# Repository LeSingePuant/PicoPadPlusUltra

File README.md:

# PicoPadPlusUltra
For convenience, these individual Gerbers are ready for upload to a PCB manufactoring website.

Feel free to clone, fork, or help me polish my keyboard/macropad design.
If you do clone, fork, or order the PicoPadPlusUltra, please let me know via Twitter or Reddit via DM or a mention. 

Cheers!

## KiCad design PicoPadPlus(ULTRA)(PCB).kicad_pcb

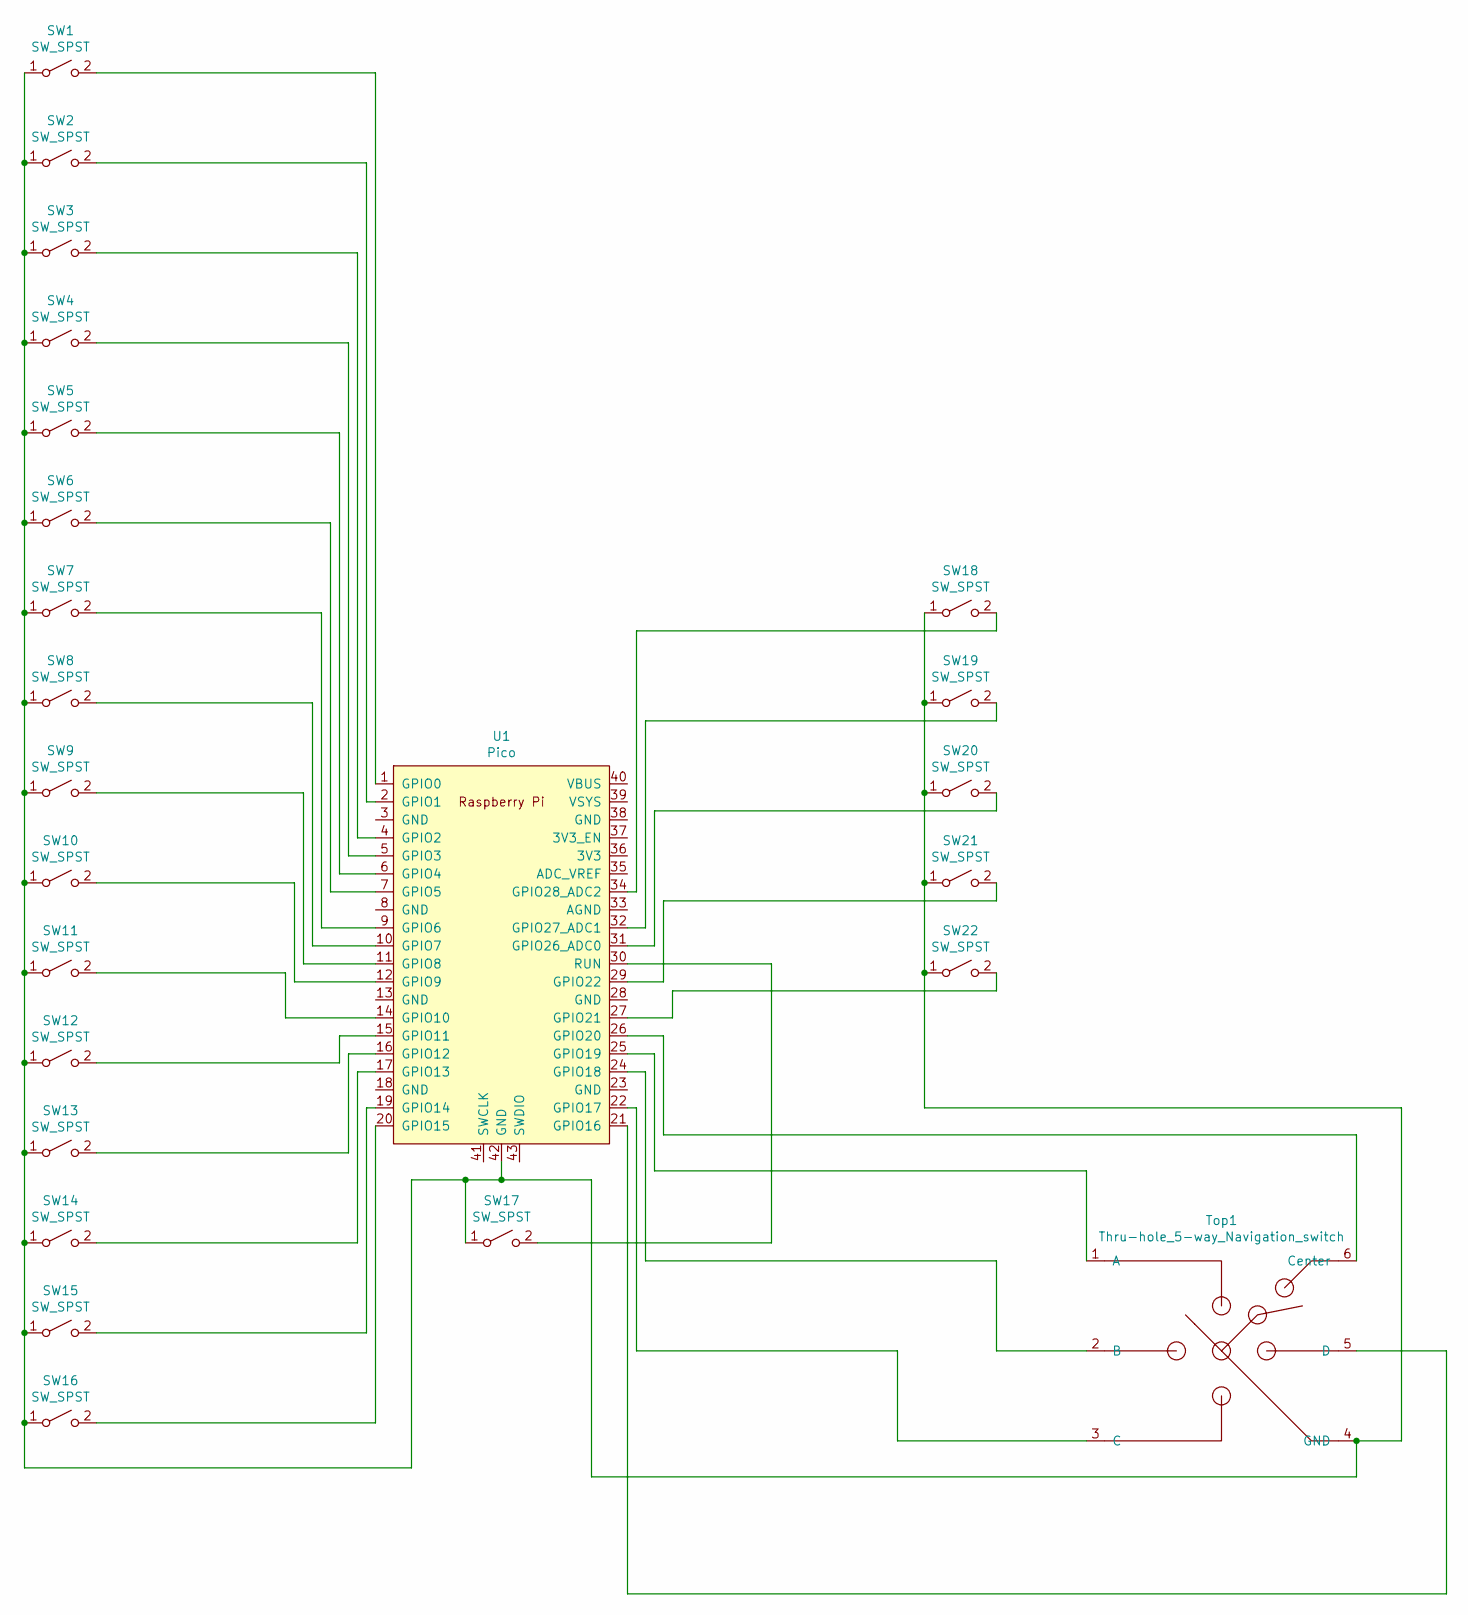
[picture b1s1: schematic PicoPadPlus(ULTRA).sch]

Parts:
SW1, SW2, SW3, SW4, SW5, SW6, SW7, SW8, SW9, SW10, SW11, SW12, SW13, SW14, SW15, SW16, SW18, SW19, SW20, SW21, SW22: SW_SPST; Kailh_socket_MX
SW17: SW_SPST; SW_PUSH_6mm
Top1: Thru-hole_5-way_Navigation_switch; SKQUCAA010_4-directional_with_Center_Push
U1: Pico; RPi_Pico_SMD_TH

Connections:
unnamed 0: SW1.1 (A), SW2.1 (A), SW3.1 (A), SW4.1 (A), SW5.1 (A), SW6.1 (A), SW7.1 (A), SW8.1 (A), SW9.1 (A), SW10.1 (A), SW11.1 (A), SW12.1 (A), SW13.1 (A), SW14.1 (A), SW15.1 (A), SW16.1 (A), SW17.1 (A), SW18.1 (A), SW19.1 (A), SW20.1 (A), SW21.1 (A), SW22.1 (A), Top1.4 (GND), U1.42 (GND); also elsewhere on the board
unnamed: SW1.2 (B), U1.1 (GPIO0)
unnamed: SW2.2 (B), U1.2 (GPIO1)
unnamed: SW3.2 (B), U1.4 (GPIO2)
unnamed: SW4.2 (B), U1.5 (GPIO3)
unnamed: SW5.2 (B), U1.6 (GPIO4)
unnamed: SW6.2 (B), U1.7 (GPIO5)
unnamed: SW7.2 (B), U1.9 (GPIO6)
unnamed: SW8.2 (B), U1.10 (GPIO7)
unnamed: SW9.2 (B), U1.11 (GPIO8)
unnamed: SW10.2 (B), U1.12 (GPIO9)
unnamed: SW11.2 (B), U1.14 (GPIO10)
unnamed: SW12.2 (B), U1.15 (GPIO11)
unnamed: SW13.2 (B), U1.16 (GPIO12)
unnamed: SW14.2 (B), U1.17 (GPIO13)
unnamed: SW15.2 (B), U1.19 (GPIO14)
unnamed: SW16.2 (B), U1.20 (GPIO15)
unnamed 17: SW17.2 (B), U1.30 (RUN); also elsewhere on the board
unnamed: SW18.2 (B), U1.34 (GPIO28_ADC2)
unnamed: SW19.2 (B), U1.32 (GPIO27_ADC1)
unnamed: SW20.2 (B), U1.31 (GPIO26_ADC0)
unnamed: SW21.2 (B), U1.29 (GPIO22)
unnamed: SW22.2 (B), U1.27 (GPIO21)
unnamed: Top1.1 (A), U1.25 (GPIO19)
unnamed: Top1.2 (B), U1.24 (GPIO18)
unnamed: Top1.3 (C), U1.22 (GPIO17)
unnamed: Top1.5 (D), U1.21 (GPIO16)
unnamed: Top1.6 (Center), U1.26 (GPIO20)

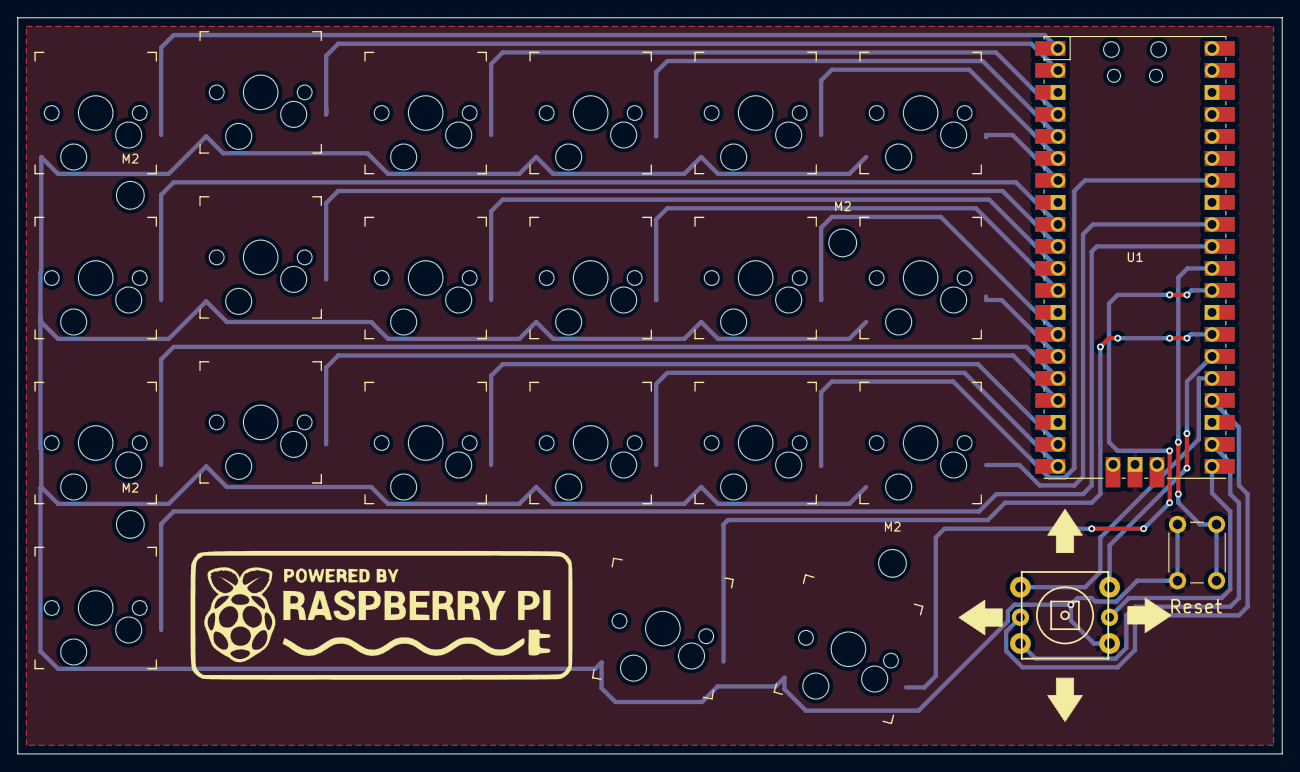
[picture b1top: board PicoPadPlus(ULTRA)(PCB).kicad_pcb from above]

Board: 2 copper layers, 146.0 x 85.0 mm, 28 parts (0 on the bottom side), 28 nets.

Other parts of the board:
M2, M2#2, M2#3, M2#4: MountingHole_3.2mm_M3
Reset: SW_SPST; SW_PUSH_6mm

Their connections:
unnamed 0: Reset.1; also elsewhere on the board
unnamed 17: Reset.2; also elsewhere on the board
